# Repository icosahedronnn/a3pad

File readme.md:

# A3PAD
A hackpad based on the Apple ///. Undebatably the best design of the 80s. Case designed in Shapr3D.

## Fully modeled
Figured out some issues from last version, so yeah... mockup is more complete.
Essentially, I gave it some pizzaz and fixed some kinks in the Apple /// design. Yeah.

Not exactly ergonomic but it's... it's stylish enough? I guess?

## PCB
Schematic.

PCB.

Not much else to say there. Tried keeping it compact.

## Firmware!!!
Uses KMK. It's pretty simple, so... ye. Shan't be TOO hard.
Encoder does volume. Press to mute.
OLED screen just for funsies. Might make a program to dynamically change it in the future. Will see.

## Production
The case top and main case are together in the same file. They're small enough, I hope.

## Bill Of Materials
Gotta know the materials part, I guess.

4x Cherry MX Falcons -- If needed I can absolutely take regular Cherry MX Reds.

4x DSA Keycaps

4x M3x16mm screws

4x M3x5x4 Heatset inserts

1x 0.91" 128x32 OLED Display

1x EC11 Rotary Encoder

1x XIAO RP2040

1x Case (fully 3d printed)

## Elsewise
Second attempt at a CAD design. Proudest work (low bar).

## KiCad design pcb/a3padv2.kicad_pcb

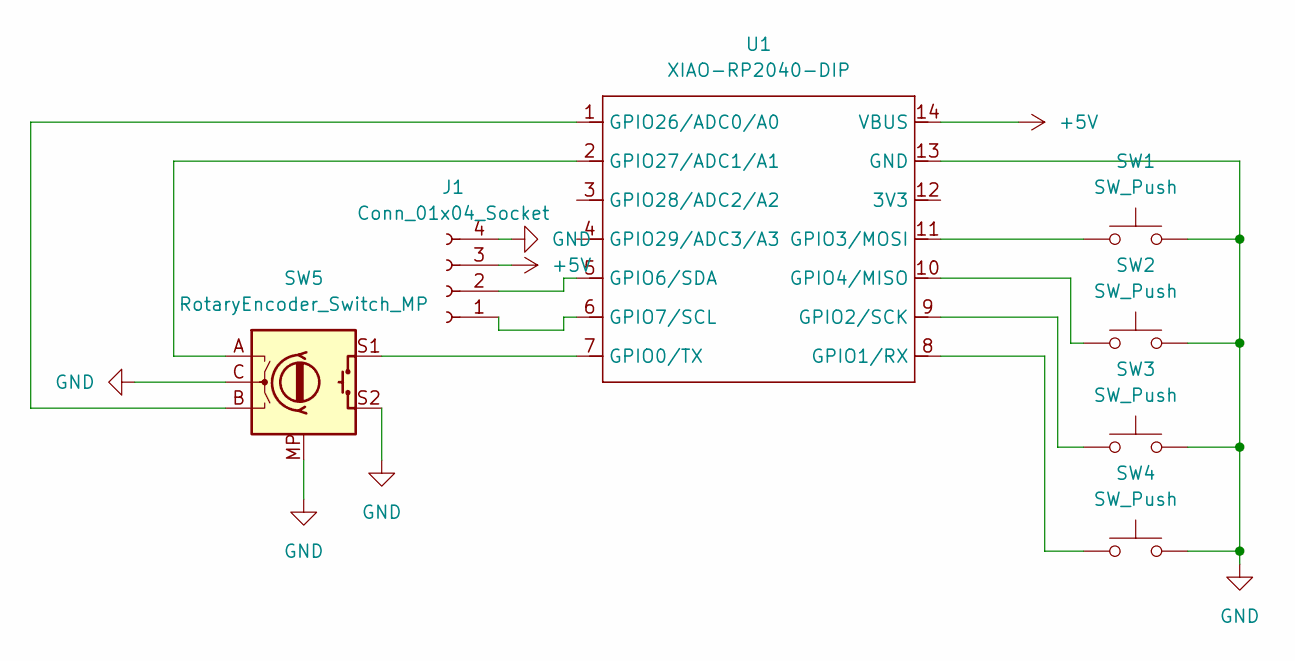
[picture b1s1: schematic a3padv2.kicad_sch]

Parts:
J1: Conn_01x04_Socket; PinSocket_1x04_P2.54mm_Vertical
SW1, SW2, SW3, SW4: SW_Push; SW_Cherry_MX_1.00u_PCB
SW5: RotaryEncoder_Switch_MP; RotaryEncoder_Alps_EC11E-Switch_Vertical_H20mm
U1: XIAO-RP2040-DIP

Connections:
+5V: J1.3, U1.14 (VBUS)
GND: J1.4, SW1.2, SW2.2, SW3.2, SW4.2, SW5.C, SW5.MP, SW5.S2, U1.13 (GND)
unnamed: J1.1, U1.6 (GPIO7/SCL)
unnamed: J1.2, U1.5 (GPIO6/SDA)
unnamed: SW5.S1, U1.7 (GPIO0/TX)
unnamed: SW4.1, U1.8 (GPIO1/RX)
unnamed: SW3.1, U1.9 (GPIO2/SCK)
unnamed: SW1.1, U1.11 (GPIO3/MOSI)
unnamed: SW2.1, U1.10 (GPIO4/MISO)
unnamed: SW5.B, U1.1 (GPIO26/ADC0/A0)
unnamed: SW5.A, U1.2 (GPIO27/ADC1/A1)

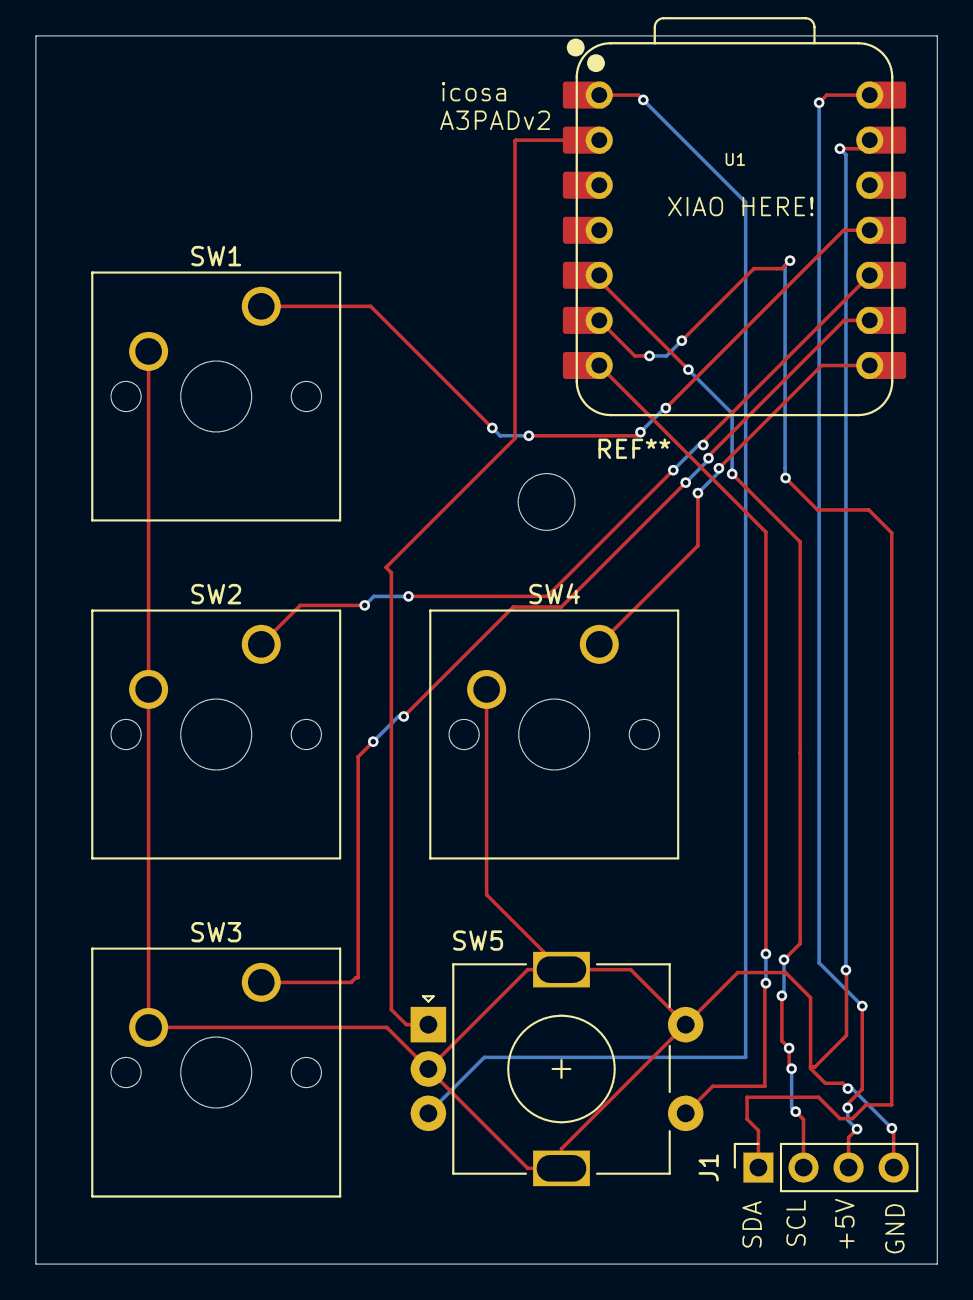
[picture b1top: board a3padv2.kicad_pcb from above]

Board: 2 copper layers, 50.8 x 69.2 mm, 7 parts (0 on the bottom side), 11 nets.

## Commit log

2026-01-12 Enhance README with detailed project descriptions
    Expanded the README with detailed sections on modeling, PCB, firmware, production, and bill of materials.
2026-01-12 Add image to the production section in readme
